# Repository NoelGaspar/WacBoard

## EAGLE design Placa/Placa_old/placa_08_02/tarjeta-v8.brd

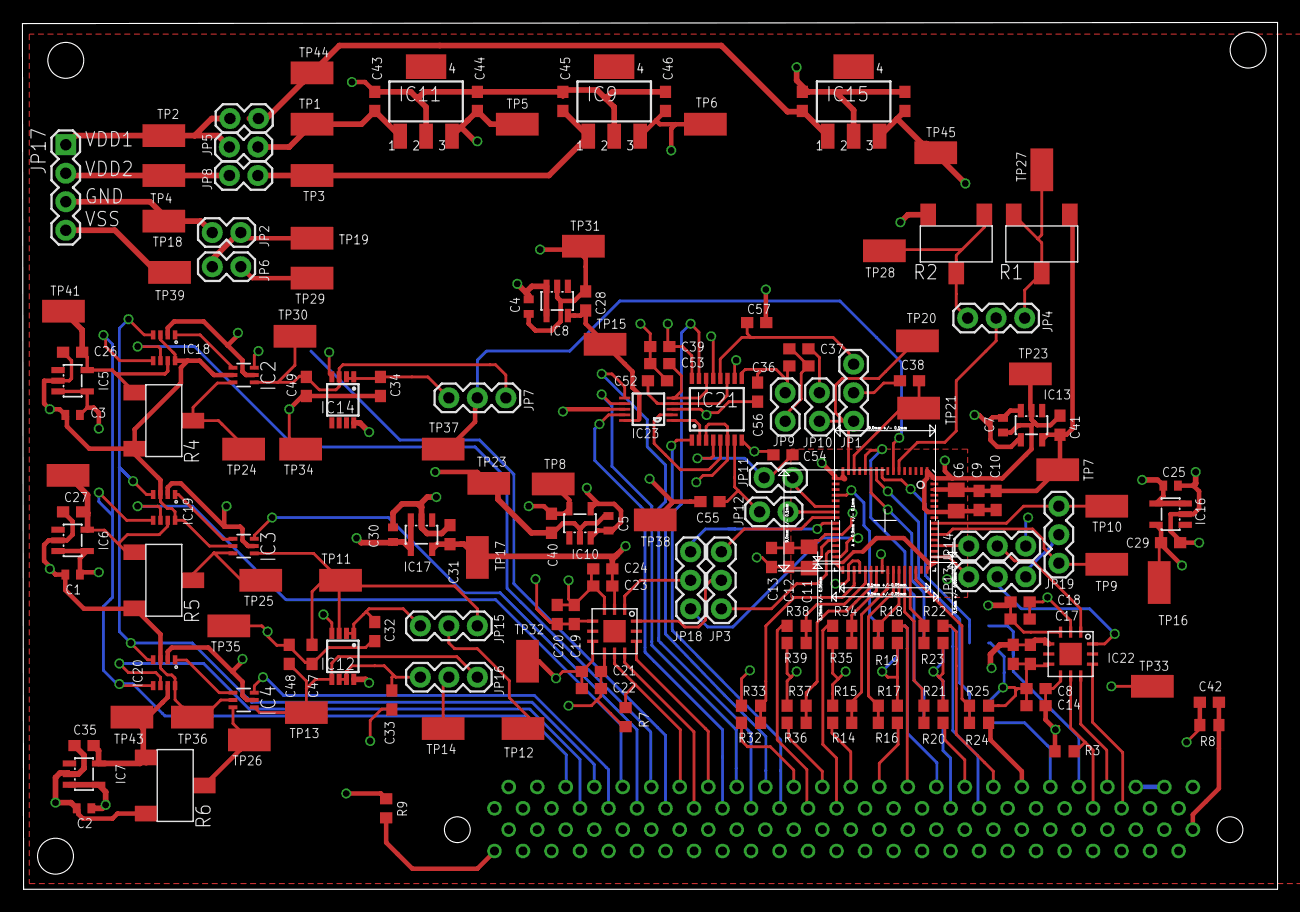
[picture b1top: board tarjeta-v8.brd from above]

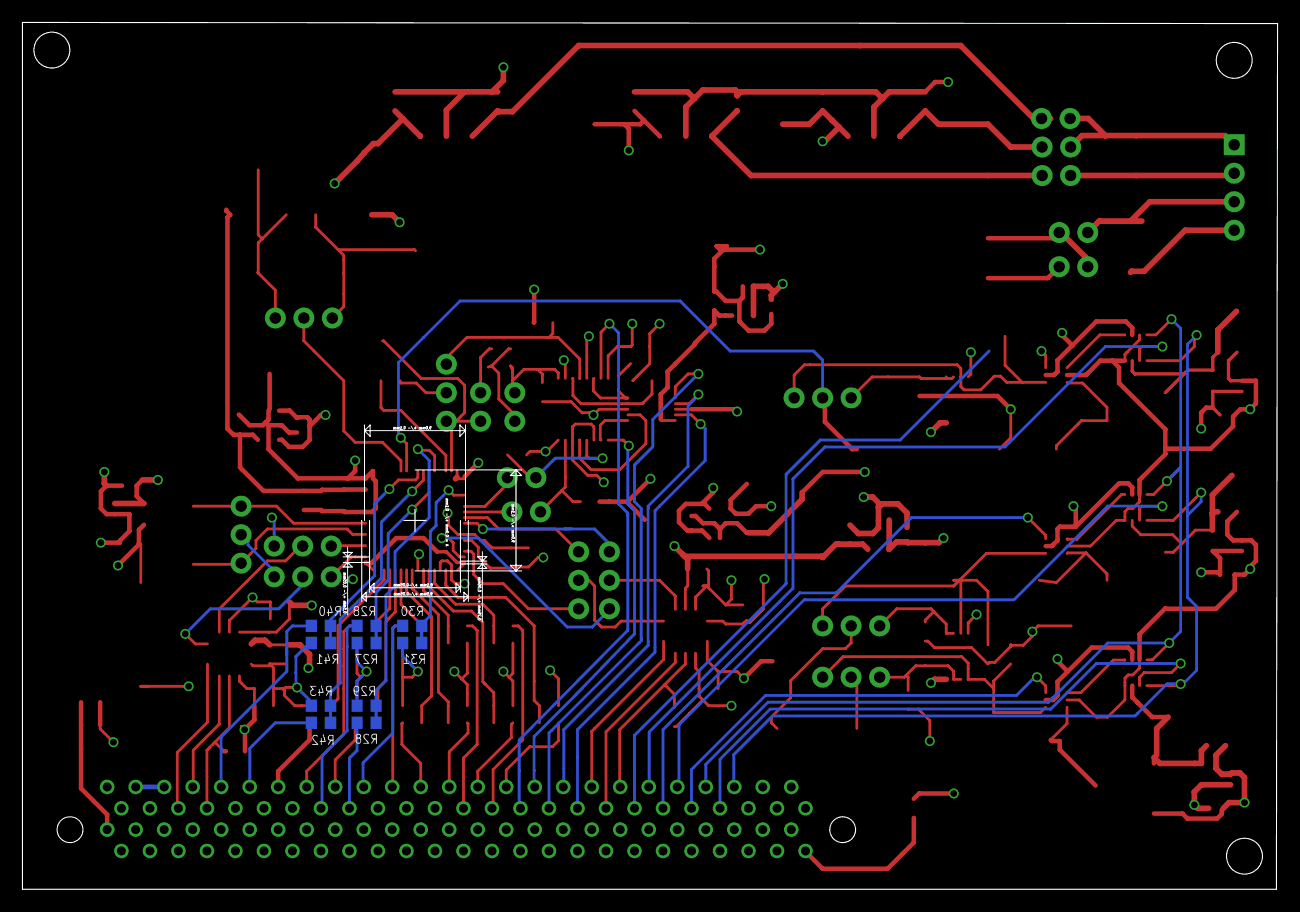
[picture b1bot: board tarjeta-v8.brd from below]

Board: 4 copper layers, 111.8 x 77.2 mm, 185 parts (10 on the bottom side), 118 nets.

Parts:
C1, C3, C5, C7, C25: C0402
C2, C4, C30: 4.7uf; C0402
C6, C11: C0805
C8, C9, C10, C12, C13, C14, C15, C16, C17, C18, C19, C20, C21, C22, C23, C24, C26, C27, C32, C33, C36, C37, C38, C40, C41, C43, C44, C45, C46, C47, C48, C49, C50, C51, C52, C53, C54, C55, C56, C57: CAP_0603; C0603
C28, C29, C31, C35: 0.1uf; C0603
C34: 4.7uf; C0603
C39: 0.1uF; C0603
C42: 1nf; C0603
IC1: THE_BEAN_2; QFN64
IC2, IC3, IC4: SC70
IC5, IC6, IC7, IC8, IC16, IC17: 1.8V; SOT23-5L_2
IC9, IC11, IC15: SOT223
IC10, IC13: 1.8; SOT23-5L_2
IC12, IC14: OP282; MSOP8
IC18, IC19, IC20: AD5160_2; SOT23-8_2
IC21: QSOP16
IC22: TQFN12
IC23: DAC7554; MSOP10
J1: HIRESO_FX_CONNECTOR; FX2-100S-1.27
JP1, JP3, JP4, JP7, JP13, JP14, JP15, JP16, JP18, JP19: JUMPER03; 1X03
JP2, JP5, JP6, JP8, JP9, JP10, JP11, JP12, JP20: JUMPER02; 1X02
JP17: JUMPER04; 1X04
R1, R2, R4, R5, R6: ST-5EW
R3, R7, R9, R14, R15, R16, R17, R18, R19, R20, R21, R22, R23, R24, R25, R26, R27, R28, R29, R30, R31, R32, R33, R36, R37, R38, R39, R40, R41, R42, R43: RES_0603; R0603
R8: 1M; R0603
R34, R35: 0; R0603
TP1, TP2, TP3, TP4, TP5, TP6, TP7, TP8, TP9, TP10, TP11, TP12, TP13, TP14, TP15, TP16, TP17, TP18, TP19, TP20, TP21, TP22, TP23, TP24, TP25, TP26, TP27, TP28, TP29, TP30, TP31, TP32, TP33, TP34, TP35, TP36, TP37, TP38, TP39, TP41, TP42, TP43, TP44, TP45: TP
U$5: TQFN12

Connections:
!CS_ADC1: IC22.P$9, J1.A44
!CS_ADC2: J1.A15, U$5.P$9
!CS_DAC: IC23.9, J1.A17
ADC1_IN+: IC22.P$12, JP13.2
ADC1_IN-: IC22.P$1, JP14.2
ADC2_IN+: JP3.2, U$5.P$12
ADC2_IN-: JP18.2, U$5.P$1
AGND: C6.2, C7.2, C9.2, C10.2, C41.2, IC1.1, IC1.16, IC1.17, IC1.32, IC1.33, IC1.48, IC1.49, IC1.58, IC1.64, IC13.2, JP2.2, JP6.2, R2.3, TP19.TP, TP22.TP
AVDD: C6.1, C9.1, C10.1, C41.1, IC1.62, IC13.5, R1.1, TP7.TP
BASELINE: IC1.56, JP19.1, TP10.TP
CAP_PRECHAR: C38.2, IC1.14, TP21.TP
CAP_PRECHAR_1: C57.1, IC21.12, JP1.1
CLK: IC1.20, R30.1, R31.2
CLK_ADC1: IC22.P$10, J1.A45
CLK_ADC2: J1.A16, U$5.P$10
CLK_DAC: IC23.6, J1.A19
CLK_PRECH1: IC1.9, R40.1, R41.2
CLK_PRECH1_T: J1.A42, R40.2
CLK_PRECH2: IC1.10, R42.1, R43.2
CLK_PRECH2_T: J1.A40, R42.2
CLK_REF: IC18.4, IC19.4, IC20.4, J1.A8
CLK_T: J1.A32, R30.2
CS_B0: IC1.41, R14.1, R15.2
CS_B0_T: J1.A26, R14.2
CS_B1: IC1.42, R16.1, R17.2
CS_B1_T: J1.A28, R16.2
CS_B2: IC1.43, R18.1, R19.2
CS_B2_T: J1.A30, R18.2
CS_B3: IC1.44, R20.1, R21.2
CS_B3_T: J1.A34, R20.2
CS_B4: IC1.45, R22.1, R23.2
CS_B4_T: J1.A36, R22.2
CS_B5: IC1.46, R24.1, R25.2
CS_B5_T: J1.A38, R24.2
CS_REF_1: IC18.6, J1.A12
CS_REF_2: IC19.6, J1.A10
CS_REF_3: IC20.6, J1.A7
DGND: C5.2, C11.2, C12.2, C13.2, C40.2, IC1.28, IC10.2, JP6.1, TP23.TP, TP29.TP
DVDD: C11.1, C12.1, C13.1, C40.1, IC1.27, IC10.5, TP8.TP
GND: C1.2, C2.2, C3.2, C4.2, C8.2, C14.2, C15.2, C16.2, C17.2, C18.2, C19.2, C20.2, C21.2, C22.2, C23.2, C24.2, C25.2, C26.2, C27.2, C28.2, C29.2, C30.2, C31.2, C32.2, C33.2, C34.2, C35.2, C39.1, C42.2, C43.2, C44.2, C45.2, C46.2, C47.2, C48.2, C49.2, C50.2, C51.2, C52.2, C53.2, C54.2, C55.2, C56.2, C57.2, IC2.2, IC3.2, IC4.2, IC5.2, IC6.2, IC7.2, IC8.2, IC9.2, IC11.2, IC15.2, IC16.2, IC17.2, IC18.3, IC18.8, IC19.3, IC19.8, IC20.3, IC20.8, IC21.8, IC21.10, IC21.13, IC22.P$3, IC22.P$6, IC23.3, J1.B2, J1.B5, J1.B6, J1.B7, J1.B8, J1.B9, J1.B10, J1.B11, J1.B12, J1.B13, J1.B14, J1.B15, J1.B16, J1.B17, J1.B18, J1.B19, J1.B20, J1.B21, J1.B22, J1.B23, J1.B24, J1.B25, J1.B26, J1.B27, J1.B28, J1.B29, J1.B30, J1.B31, J1.B32, J1.B33, J1.B34, J1.B35, J1.B36, J1.B37, J1.B38, J1.B39, J1.B40, J1.B41, J1.B42, J1.B43, J1.B44, J1.B45, J1.B47, JP2.1, JP14.1, JP17.3, R4.3, R5.3, R6.3, R8.1, R9.1, R15.1, R17.1, R19.1, R21.1, R23.1, R25.1, R27.1, R29.1, R31.1, R33.1, R35.1, R37.1, R39.1, R41.1, R43.1, TP18.TP, TP31.TP, TP32.TP, TP33.TP, TP34.TP, TP35.TP, TP36.TP, TP38.TP, U$5.P$3, U$5.P$6
HOLD: IC1.37, R38.1, R39.2
HOLD_T: J1.A23, R38.2
MUX_DAC_EN: IC21.15, J1.A21
MUX_DAC_SEL: IC21.1, J1.A20
MUX_REF_1: IC2.6, J1.A13
MUX_REF_2: IC3.6, J1.A11
MUX_REF_3: IC4.6, J1.A9
unnamed: C36.2, C37.1, JP9.2
unnamed: J1.B1, R9.2
unnamed: C37.2, JP10.1
unnamed: J1.A46, J1.A48
unnamed: IC4.1, IC20.1
unnamed: C38.1, JP1.2
unnamed: JP13.1, JP19.2
unnamed: C42.1, J1.B50, R8.2
unnamed: IC2.1, IC18.1
unnamed: IC3.1, IC19.1
OP_MODE: IC1.11, R26.1, R27.2
OP_MODE_T: J1.A35, R26.2
OUT_S: IC1.35, R32.1, R33.2
OUT_S_T: J1.A22, R32.2
POT_R1: JP4.3, R1.2, R1.3, TP27.TP
POT_R2: JP4.1, R2.1, R2.2, TP28.TP
POT_R4: IC2.3, R4.2, TP24.TP
POT_R5: IC3.3, R5.2, TP25.TP
POT_R6: IC4.3, R6.2, TP26.TP
REFIN_DAC: C28.1, IC8.5, IC23.10, TP15.TP
REF_ADC: C17.1, C18.1, C23.1, C24.1, C31.1, IC17.5, IC22.P$2, TP17.TP, U$5.P$2
RES_BIAS_EXT: IC1.6, JP4.2
RST: IC1.38, R36.1, R37.2
RST_CSA: IC1.12, R28.1, R29.2
RST_CSA_T: J1.A33, R28.2
RST_T: J1.A24, R36.2
SDI_DAC: IC23.7, J1.A18
SDI_REF: IC18.5, IC19.5, IC20.5, J1.A6
SDO_ADC1: IC22.P$8, J1.A43, R3.1
SDO_ADC2: J1.A14, R7.1, U$5.P$8
SGN: IC1.39, R34.1, R35.2
SGN_T: J1.A25, R34.2
V0NDAC: IC21.5, IC23.2
V0PDAC: IC21.2, IC23.1
V1NDAC: C53.1, IC21.14, IC23.5
V1PDAC: C52.1, IC21.11, IC23.4
VDD: C1.1, C2.1, C3.1, C39.2, C44.1, IC2.5, IC3.5, IC4.5, IC5.3, IC5.4, IC6.3, IC6.4, IC7.3, IC7.4, IC11.3, IC18.2, IC19.2, IC20.2, IC21.16, IC23.8, TP5.TP
VDD2: C5.1, C7.1, C46.1, IC9.3, IC10.3, IC10.4, IC13.3, IC13.4, TP6.TP
VDD3: C4.1, C15.1, C16.1, C19.1, C20.1, C25.1, C30.1, C51.1, IC8.3, IC8.4, IC12.8, IC14.8, IC15.3, IC16.3, IC16.4, IC17.3, IC17.4, IC22.P$4, TP45.TP, U$5.P$4
VDD_REF_1: C26.1, IC5.5, IC18.7, R4.1, TP41.TP
VDD_REF_2: C27.1, IC6.5, IC19.7, R5.1, TP42.TP
VDD_REF_3: C35.1, IC7.5, IC20.7, R6.1, TP43.TP
VDD_SUPPLY_1: C43.1, IC11.1, JP5.1, TP1.TP
VDD_SUPPLY_2: C45.1, IC9.1, JP8.1, TP3.TP
VDD_SUPPLY_3: C50.1, IC15.1, JP20.1, TP44.TP
VDD_SUPPLY_IN_1: JP5.2, JP17.1, JP20.2, TP2.TP
VDD_SUPPLY_IN_2: JP8.2, JP17.2, TP4.TP
VI+_FIL: IC1.22, JP11.2
VI+_FIL_DAC: C54.1, IC21.4, JP11.1
VI-_FIL: IC1.23, JP12.2
VI-_FIL_DAC: C55.1, IC21.7, JP12.1
VICM: IC1.40, IC21.3, IC21.6, JP15.2, TP12.TP
VICM_BUFF: C32.1, IC12.1, IC12.2, JP15.1
VICM_MUX: C47.1, IC3.4, IC12.3, JP15.3, TP11.TP
VIN_CSA: IC1.15, JP1.3, JP10.2, TP20.TP
VIN_CSA_1: C36.1, C56.1, IC21.9, JP9.1
VL_ADC: C8.1, C14.1, C21.1, C22.1, C29.1, IC16.5, IC22.P$7, R3.2, R7.2, TP16.TP, U$5.P$7
VO+_BP_FIL: IC1.24, JP3.3
VO+_CH: IC1.50, JP13.3
VO+_FIL: IC1.30, JP3.1
VO-_BP_FIL: IC1.25, JP18.3
VO-_CH: IC1.52, JP14.3
VO-_FIL: IC1.31, JP18.1
VOCM: IC1.34, IC1.36, JP16.2, TP14.TP
VOCM_1: C49.1, IC2.4, IC14.3, JP7.3, TP30.TP
VOCM_BUFF: C33.1, IC12.6, IC12.7, JP16.1
VOCM_MUX: C48.1, IC4.4, IC12.5, JP16.3, TP13.TP
VOUT_CSA: IC1.54, JP19.3, TP9.TP
VSS: IC12.4, IC14.4, JP17.4, TP39.TP
V_REF_PRECHAR: IC1.7, JP7.2, TP37.TP
V_REF_PRECHAR_BUFF: C34.1, IC14.1, IC14.2, JP7.1
